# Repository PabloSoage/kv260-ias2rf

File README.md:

# KV260-IAS2RF — an RF front-end carrier for the AMD Kria KV260

**Status (12 November 2026): schematic and layout complete, on 8 layers. The board is fully routed, with zero
DRC errors and zero schematic-parity problems. It has not been fabricated, and no hardware has
been validated.** A few review items remain before an order (see [Status](#status)).

> **Rev06 (14 November 2026), now on `main`; Rev05 is tag `rev05`.** Rev06 gives Gigabit Ethernet its own FPGA pins, so the IAS1 link keeps
> both uplink lanes and its downlink and Ethernet adds about 1 Gb/s on top: either path works alone, both
> together carry about 3 Gb/s, with failover in the gateware ([CONTROL_SPEC §8](docs/CONTROL_SPEC.md),
> [fpga/eth/REV06.md](fpga/eth/REV06.md)). It also adds a 5 V fan header for enclosure v2
> ([ENCLOSURE §6](docs/ENCLOSURE.md)). Routed with zero DRC errors and zero parity problems. The full pre-order
> review (RF, power, ESD, thermal, routing, the enclosure's 3-D FEA with the boards, and the two-FPGA system
> simulation) is [docs/REV06_REVIEW.md](docs/REV06_REVIEW.md).

An adapter board for the **AMD Kria KV260 Vision AI Starter Kit**. It plugs into the KV260's IAS1
camera connector and carries the converters, a common clock and a front-end FPGA. It serves two
signal chains:

- **Software-defined radio**: HF, AM, FM, airband, amateur bands and PMR446. Receive, and
  transmit on the bands a licence covers.
- **Radar at 10.5 GHz**: the IF of the X-band chain from the open
  [AERIS-10 / PLFM_RADAR](https://github.com/NawfalMotii79/PLFM_RADAR) project, with ADAR1000
  beamforming. The 10.5 GHz chain itself is reused from AERIS-10, not redesigned here. The board
  is sized for 8 ADAR1000s (32 channels), so it covers both the Nexus variant (4 chips) and the
  Extended one (8 chips).

> ### The finding that shapes the whole project
>
> The **IAS0 (J7) connector on the KV260 does not reach the programmable logic**: its MIPI lanes
> run into an AP1302 ISP soldered on the carrier card. Only **IAS1 (J8)** is wired straight to
> the SOM. On top of that, **the KV260 has no 40-pin Raspberry Pi header** (J9 is a 15-pin
> camera connector), and **the GTH transceivers are not exposed**.
>
> The real I/O budget between a KV260 and an external board is **8 differential pairs and about
> 14 single-ended signals**. That is why the board has its own FPGA. The evidence and sources are
> in [docs/BLOCKERS_AND_RISKS.md](docs/BLOCKERS_AND_RISKS.md).

---

## The board at a glance

| | |
|---|---|
| Size | 119 × 132 mm, 140 × 132 with the RJ45's tab. It mounts on the KV260's IAS connectors and corner holes and overhangs to one side ([INTERFACE_SPEC §5.3](docs/INTERFACE_SPEC.md)) |
| Stackup | 8 layers, JLCPCB JLC08161H-2116C: signal, GND, signal, split power, GND, signal, GND, signal ([LAYOUT §3](docs/LAYOUT.md); 6 layers until 12 Nov, [compared in EIGHT_LAYERS](docs/EIGHT_LAYERS.md)) |
| Parts | 534 fitted: the top face, plus 20 on the bottom face under the FPGA (LVDS terminations and VCCINT caps); 4 DNP for the Ethernet option |
| Front-end FPGA | Xilinx XC7A50T-2FTG256I (the same part as AERIS-10) with a 128 Mb QSPI flash, plus JTAG |
| Radar ADC | AD9484, 8 bit, 400 MSPS, driven by two cascaded AD8352s |
| SDR ADC | AD9253, 14 bit, two channels at 62.5 MSPS (one LVDS lane each) |
| Radar DAC | AD9708, with reconstruction filter and balun |
| SDR DAC | AD9767, dual 14 bit, two output chains |
| Clock | Si549 programmable XO (400 or 500 MHz, GPS-disciplinable) into an ADCLK948 LVPECL fan-out |
| RF routing | Four M3SWA2-34DR+ SPDT switches and ten edge SMAs, plus two clock SMAs |
| Link to the Kria | IAS1 (Hirose BM20B), five LVDS pairs at up to 1 Gb/s each, AC-coupled; the Pmod J2 for control |
| Ethernet (option) | Gigabit RJ45 through an RTL8211FSI SGMII PHY, which shares two of the link's pairs: fit C1218–C1221 and remove C101, C102, C107, C108 to use it ([CONTROL_SPEC §7](docs/CONTROL_SPEC.md)) |
| To AERIS-10 | 2×20 IDC ribbon for eight ADAR1000s |
| Power | 12 V in; buck and LDO tree for 5 V, 3.3 V, 2.5 V, 1.8 V and 1.0 V, plus −3.3 V for the switches |

```mermaid
flowchart LR
  KV260["Kria KV260<br/>(K26 SOM)"] <-- "IAS1: 5 LVDS pairs<br/>Pmod: control" --> FPGA["XC7A50T<br/>front-end FPGA"]
  FPGA <-- LVDS --> ADCR["AD9484<br/>radar ADC"]
  FPGA <-- LVDS --> ADCS["AD9253<br/>SDR ADC"]
  FPGA --> DACR["AD9708<br/>radar DAC"]
  FPGA --> DACS["AD9767<br/>SDR DAC"]
  CLK["Si549 + ADCLK948<br/>clock"] --> ADCR & ADCS & DACR & DACS & FPGA
  ADCR & ADCS & DACR & DACS <--> RF["RF switches<br/>10 SMAs"]
  FPGA <-- "IDC ribbon" --> AERIS["AERIS-10<br/>8 × ADAR1000"]
  RF <--> AERIS
```

| Top | Bottom |
|---|---|
|  |  |

The renders come from KiCad. Some parts have no 3D model, so they show only their pads (the FPGA's
BGA, for one).

---

## Schematics and layout

- **[Schematic, all 10 sheets (PDF)](docs/CSI2-KRIA-KV260_Rev04_schematic.pdf)**
- **[Layout, the eight copper layers and both silkscreens (PDF)](docs/CSI2-KRIA-KV260_Rev04_layout.pdf)**
- KiCad 10 sources: [`CSI2-KRIA-KV260_Rev01.kicad_pro`](CSI2-KRIA-KV260_Rev01.kicad_pro), the root
  schematic and [`rev03/`](rev03/) (the nine sheets), the board
  [`CSI2-KRIA-KV260_Rev01.kicad_pcb`](CSI2-KRIA-KV260_Rev01.kicad_pcb), and the project's own
  symbols and footprints in [`symbols/`](symbols/) and [`footprints/`](footprints/). The file names
  keep the Rev01 name of the board they started from, and the sheets sit in `rev03/` where they
  were drawn; the contents are Rev04 (the 8-layer board, 12 Nov 2026).

| Sheet | Contents | Specification |
|---|---|---|
| [Root](docs/img/sch/ROOT.png) | Sheet hierarchy and the interface nets | [ARCHITECTURE](ARCHITECTURE.md) |
| [IAS_LINK](docs/img/sch/IAS_LINK.png) | The Hirose connectors, AC coupling and terminations of the link | [IAS_LINK_SPEC](docs/IAS_LINK_SPEC.md) |
| [CLOCK](docs/img/sch/CLOCK.png) | Si549, reference select and LVPECL fan-out | [CLOCK_SPEC](docs/CLOCK_SPEC.md) |
| [ADC_RADAR](docs/img/sch/ADC_RADAR.png) | AD9484 and its two AD8352 drivers | [ADC_RADAR_SPEC](docs/ADC_RADAR_SPEC.md) |
| [ADC_SDR](docs/img/sch/ADC_SDR.png) | AD9253, two channels | [ADC_SDR_SPEC](docs/ADC_SDR_SPEC.md) |
| [DAC_RADAR](docs/img/sch/DAC_RADAR.png) | AD9708, filter and balun | [DAC_RADAR_SPEC](docs/DAC_RADAR_SPEC.md) |
| [DAC_SDR](docs/img/sch/DAC_SDR.png) | AD9767 in interleaved mode, two output chains | [DAC_SDR_SPEC](docs/DAC_SDR_SPEC.md) |
| [ROUTING](docs/img/sch/ROUTING.png) | Four RF switches and the SMAs | [ROUTING_SPEC](docs/ROUTING_SPEC.md) |
| [CONTROL](docs/img/sch/CONTROL.png) | The front-end FPGA: banks, configuration, Pmod, AERIS ribbon, housekeeping | [CONTROL_SPEC](docs/CONTROL_SPEC.md) |
| [POWER](docs/img/sch/POWER.png) | The power tree | [POWER_SPEC](docs/POWER_SPEC.md) |

---

## Status

| Check | Result |
|---|---|
| ERC | 0 errors; 7 warnings, all explained: configuration and XADC pins tied to power on purpose ([CONTROL_SPEC §5](docs/CONTROL_SPEC.md)) |
| DRC, zones refilled | **0 violations, 0 unrouted connections, 0 schematic-parity problems** (12 Nov, on 8 layers) |
| Signal and power integrity | Reviewed on 11 Nov and re-run on 8 layers on 12 Nov, ideal / 6 / 8 layers side by side ([EIGHT_LAYERS.md](docs/EIGHT_LAYERS.md), [SIGNAL_INTEGRITY.md](docs/SIGNAL_INTEGRITY.md)): SMA launch in openEMS (S11 −30.9 dB at 1 GHz with the ESD diode), LVDS eyes within 1–26 mV of ideal except LINK_RX_D0 (−52 mV), worst intra-pair skew 9 ps, VCCINT under its target to 100 MHz with four caps under the BGA; ESD protection on every SMA, the Pmod and JTAG, a GND via within 3 mm of every LVDS layer change, exposed-pad vias and an edge fence |
| Planes | L2 and L5 carry only ground, no supply track (`_work/layout/planechk.py`); every supply pin reaches its island (the DRC's zero unrouted) |
| Mechanical fit | Registered on AMD's 3D model of the KV260: the mounting holes land within 5 µm ([INTERFACE_SPEC §5.3](docs/INTERFACE_SPEC.md)) |

**Open before ordering** ([docs/LAYOUT.md §6.2–6.3](docs/LAYOUT.md)):

1. **The rest of the board, reviewed on 12 Nov** ([SIGNAL_INTEGRITY §9](docs/SIGNAL_INTEGRITY.md)).
   - **Fixed.** The router had necked supply tracks and the bucks' switch nodes to 0.1 mm: 1.6 A
     through 0.1 mm at U1001, and a 251 mV drop on the ADCs' +1V8_A. The supply tracks are now
     widened (865 mm at ≥ 0.5 mm, against 119), and +1V8_A starts at 1.85 V to cover what is
     left of the drop.
   - **Analogue nodes.** Digital tracks beside the analogue nodes are down to 81 mm within
     0.3 mm, from 91. Most of what was left was where the SDR DAC's filters crossed the DAC bus.
     On 12 Nov DAC2's filter was re-placed next to its balun and DAC1's middle node re-routed as
     a pair: their digital neighbours went from 59 mm to 14 mm. DAC2's common mode at the balun
     fell by 9–21 dB. On 13 Nov DAC1's filter followed, onto the bottom face under T801 (its
     middle node 51 → 3 mm, common mode 1–6 dB lower), the reference oscillator's pair was
     coupled and matched, and the SDR ADC's input network was simulated: its copper costs
     nothing in band, so it stays.
   - **Thermal.** 7.5 W on 134 cm² in still air (with the Ethernet PHY): +27 °C mean and +51 °C at the clock buffer. Fine
     on the bench. A vehicle install needs airflow or a path to the enclosure.
2. **Ten of the 19 LVDS pairs are not coupled** (11 of 22 counting U401's three clock pairs:
   `CLK_ADCS` and `CLK_FPGA` were re-routed as coupled pairs on 12 Nov, `CLK_FPGA` after its
   four pad resistors were re-placed together; SIGNAL_INTEGRITY §9.4). Since 12 Nov the board has 8 layers and nine pairs
   run coupled at 100 Ω end to end ([EIGHT_LAYERS.md](docs/EIGHT_LAYERS.md)). The other ten are
   two 50 Ω legs matched to ±5 ps, within 1–26 mV of their ideal eye except LINK_RX_D0 (−52 mV).
   LINK_RX leaves bank 34, the only 2.5 V bank, in the BGA's south-east corner, and crosses every
   ADC pair to AC capacitors spread 9 mm apart; moving it to the bank's outer balls was tried on
   12 Nov and dropped (the corner has no room left for the vias). Coupling it would need the
   capacitors at J101 moved together first.
3. **ADCR data to DCO skew, −90 to +5 ps** (was −177 to −28). DCO's legs are swapped at the FPGA
   (N14 = DCO_N, P14 = DCO_P) so the pair reaches the AD9484 the right way round without going
   round the chip: 39 mm instead of 51. **The gateware must invert that clock** (ISERDESE2
   `IS_CLK_INVERTED`, or capture on the other edge) ([CONTROL_SPEC §1](docs/CONTROL_SPEC.md)).
   The rest is inside IDELAYE2's range and calibrated per bit.
4. **Order the 2116C stack explicitly** (JLC08161H-2116C): the widths are solved for it
   ([FABRICATION.md](docs/FABRICATION.md)). Five 8-layer bare boards: $287.96 at 140 × 132 mm with the Ethernet tab ($282.92 without it, $236.88 on 6 layers).
5. **The Kria side of the link is `DIFF_SSTL12`, not `LVDS_12`** (UG571 read on 12 Nov,
   [INTERFACE_SPEC §6.3](docs/INTERFACE_SPEC.md)). No `LVDS_12` exists. `LVDS` at 1.2 V is
   input-only with no internal termination. `DIFF_SSTL12` has on-die split termination
   (`RTT_48`, about 96 Ω biased at 0.6 V) and drives through `RDRV_60_60`. No change to the board.
   Still to confirm in DS925: its input threshold and the −2LV rate ceiling. The link carries 2 Gb/s towards the Kria and 1 Gb/s back (two of its five
   pairs are clocks), with a ceiling of about 1.25 Gb/s per pair set by the silicon
   ([IAS_LINK_SPEC §7](docs/IAS_LINK_SPEC.md)).
6. **3-D full-wave sub-models (openEMS), not yet inside the eye simulation.**
   - **Layer change L1 to L6.** The pair reflects under −29 dB up to 1.25 GHz, with or without
     ground vias. Without them 7 % of the common mode's power leaks into the plane cavity; with
     two, 1 %.
   - **BGA escape.** The 0.10 mm necks reflect under −24 dB at 1.25 GHz.
   - **Two pairs side by side.** The board's worst run couples 1.9 % of a 300 ps edge onto the
     nearest leg, not the 7 % the 2-D estimate gave.
   - **J101's footprint**, from the Hirose pins to the AC capacitors: reflection under −25 dB to 1.25 GHz,
     but the legs' different escapes turn 9 % of the differential wave into common mode.

   Done, in [SIGNAL_INTEGRITY §9.6](docs/SIGNAL_INTEGRITY.md):
   - **Receive budgets.** Radar: full scale −17.6 dBm, NF 26.8 dB. SDR: full scale −2.4 and
     −3.0 dBm, NF 22 dB. On both, the ADC is 80–92 % of the noise.
   - **Transmit levels** and **the DAC filters with their copper.**
   - **The board's thermal map**, with junctions for every part that has data. At 25 °C in still
     air, the hottest junction is the ADCLK948 at 84 °C and the FPGA is at 63 °C. A vehicle
     needs airflow: a heatsink on the ICs and the regulators, with a fan, keeps every junction
     under 92 °C at 70 °C ambient.

   The first boards are for evaluation.
7. **The AERIS-10 end of the ribbon does not exist yet.**
8. **No firmware.** The FPGA design for the front end and the Kria side of the link are not
   written yet.

**Cost** ([docs/JLCPCB_QUOTE.md](docs/JLCPCB_QUOTE.md), bare boards re-quoted on 8 layers on 12 Nov 2026): about **$2,070 for two
assembled boards** and $4,240 for five, three quarters of it parts. Seven parts are out of stock at
LCSC today (the ADCs, the RF switches, the clock buffer, the DAC, a balun and the drivers): JLCPCB's
global sourcing or consigned parts cover them.

---

## Documentation

| Document | Contents |
|---|---|
| **[docs/VEHICLE_PLATFORM.md](docs/VEHICLE_PLATFORM.md)** | **System view.** The whole vehicle project: LiDAR, SDR, radar, OBD2 |
| [docs/SHOPPING_LIST.md](docs/SHOPPING_LIST.md) | Parts and checklist per stage, with indicative costs |
| [ARCHITECTURE.md](ARCHITECTURE.md) | Master document for this board: the Rev03 architecture and BOM |
| [docs/BLOCKERS_AND_RISKS.md](docs/BLOCKERS_AND_RISKS.md) | The five blockers, closed, with evidence and sources, plus the open risks |
| [docs/INTERFACE_SPEC.md](docs/INTERFACE_SPEC.md) | Pin map for J8 and the Pmod, the mechanical envelope, the adapter registered on the KV260 model |
| [docs/POWER_AND_STACKUP.md](docs/POWER_AND_STACKUP.md) | Per-rail current budget and the original 6-layer stackup with computed trace widths |
| [docs/SYMBOLS.md](docs/SYMBOLS.md) | The project's symbols, each from its datasheet, cross-checked against a second source where one exists |
| Sheet specifications | One per schematic sheet, in the table above: every value and where it comes from |
| [docs/LAYOUT.md](docs/LAYOUT.md) | The board: outline, stackup, rules, the split power layer, placement, routing and the LVDS review |
| [docs/EIGHT_LAYERS.md](docs/EIGHT_LAYERS.md) | The 8-layer board against the 6-layer one: stacks, every check side by side, eyes, skew, PDN, SMA, and what the same corrections would give on 6 layers |
| [docs/SIGNAL_INTEGRITY.md](docs/SIGNAL_INTEGRITY.md) | The RF/high-speed review (11 Nov) and the 8-layer re-run (12 Nov, §8): impedance, SMA launch (openEMS), LVDS eyes (ngspice), PDN impedance and DC drop, crosstalk, return vias, what is still a compromise; figures and data in [docs/sim/](docs/sim/) |
| [docs/FABRICATION.md](docs/FABRICATION.md) | Ordering from JLCPCB: the output script, the order form, what is left for the day of the order |
| [docs/JLCPCB_QUOTE.md](docs/JLCPCB_QUOTE.md) | What the JLCPCB order would cost (10 Nov 2026, bare boards on 8 layers 12 Nov, re-quoted with the Ethernet tab 13 Nov): boards, assembly fees and every part with its LCSC link and price. About $2,125 for two assembled boards, $4,310 for five |
| [docs/ROADMAP.md](docs/ROADMAP.md) | Staged plan with verifiable exit criteria |
| [docs/AUDIT_Rev01.md](docs/AUDIT_Rev01.md), [docs/HISTORY_Rev01.md](docs/HISTORY_Rev01.md) | What the inherited files contained, and the record of the earlier work |

---

## Repository layout

| Path | Contents |
|---|---|
| `CSI2-KRIA-KV260_Rev01.*`, `rev03/` | The KiCad project: root schematic, nine sheets, board |
| `symbols/`, `footprints/` | The project's own libraries |
| `docs/` | Specifications, layout and fabrication notes, renders and the PDFs |
| `_work/` | The scripts behind every finding and every step of the layout: symbols and footprints, sheet checks, placement (`_work/layout/build_board.py`), plane and LVDS checks, fabrication outputs |
| `fab/` | Not tracked. `python _work/fab/make_fab.py` writes Gerbers, drill, BOM and CPL there for JLCPCB |
| `PCB/`, `Documents/` | The original Allied Vision sources (Altium) and their outputs, untouched |
| `_backup_original/`, `_deprecated/` | Snapshots of the inherited files and the sheets removed from the project |

Reproducing the checks and the outputs (KiCad 10):

```bash
kicad-cli sch erc --severity-all CSI2-KRIA-KV260_Rev01.kicad_sch
kicad-cli pcb drc --schematic-parity --refill-zones --severity-all CSI2-KRIA-KV260_Rev01.kicad_pcb
python _work/fab/make_fab.py                                   # fab/: Gerbers, drill, BOM, CPL
python _work/fab/quote.py                                      # today's LCSC prices and stock; refreshes docs/JLCPCB_QUOTE.md
python _work/layout/lvds_skew.py CSI2-KRIA-KV260_Rev01.kicad_pcb  # LVDS delays, skew and stubs; --stubs PS lists the branches (needs shapely)
```

---

## Related work

The DSP core this board will need already exists, runs on real silicon and is published
separately:

**[scanner64](https://github.com/PabloSoage/scanner64)**: a real-time multichannel DDC bank for
the KV260's PL. Measured on the board: 100.05 MSPS sustained, no samples dropped across
200 million, bit-exact against its Python model, 8.38 mW per channel, 169.9 MHz Fmax post-route.

That project answers, with hardware, the question this board is built around: whether the PL can
sustain a converter stream in real time. It can.

---

## Where the project came from, and attribution

This is a **fork** of the open hardware design
[Allied Vision Adapter Board CSI-2 for Kria KV260](https://github.com/alliedvision), published
under the MIT licence (see [LICENSE](LICENSE)). What is kept from that design:

- the board's mechanical fit to the KV260 (the outline was extended)
- the two Hirose BM20B(0.8)-34DP connectors (IAS0 / IAS1) and their wiring to the SOM

Everything else (the MIPI camera electronics, level shifters, USB power) was removed and replaced
by the RF chain described here. **This repository no longer produces an Allied Vision camera
adapter board.** If that is what you want, use the original project.

---

## Simulation results

Every figure compares three cases: an **ideal** line, the board on **6 layers** (JLC06161H-2116A,
11 November 2026) and on **8 layers** (JLC08161H-2116C, the board in this repository), all run
through the same scripts. The full comparison is in [docs/EIGHT_LAYERS.md](docs/EIGHT_LAYERS.md),
the method in [docs/SIGNAL_INTEGRITY.md](docs/SIGNAL_INTEGRITY.md).

| Check | 6 layers | 8 layers |
|---|---|---|
| Pairs routed coupled | 0 of 19 | 9 of 19 |
| Worst intra-pair \|P−N\| | 84 ps | 9 ps |
| Eye lost to routing (routed − ideal) | mean −22 mV, worst −113 mV | mean −8 mV, worst −52 mV |
| Zero-crossing spread added | mean 5 ps, worst 29 ps | mean 1 ps, worst 10 ps |
| Layer changes with no GND via within 3 mm | 1 of 186 | 0 of 89 |
| Other pairs' legs within 0.25 mm | 97.6 mm | 65.8 mm |
| Signal tracks on L4 under the BGA | 64 segments | 3 (supply stubs) |
| ADCR data − DCO | −88 … −23 ps | −90 … +5 ps (DCO re-routed 12 Nov; IDELAY absorbs it) |
| VCCINT impedance, max in band / at 100 MHz (target 120 mΩ) | 51 / 61 mΩ | 41 / 63 mΩ |
| DC drop +2V5 at 601 mA | 173–185 mV | 122–129 mV |
| SMA launch S11 at 1 / 3 GHz, with the ESD diode | −30.6 / −13.5 dB | −30.9 / −13.7 dB |

**LVDS eyes** (ngspice, PRBS7 at 1 Gb/s, each leg's copper by layer and width). The ideal line
depends on each board's pair length and termination, so each board is shown against its own ideal.

| Pair | 6 layers: ideal / routed | 8 layers: ideal / routed |
|---|---|---|
| LINK_RX_D1 | 575 / 559 mV, 75 / 77 ps | 385 / 372 mV, 41 / 51 ps |
| LINK_RX_D0 | 607 / 559 mV, 35 / 30 ps | 509 / 457 mV, 25 / 31 ps |
| LINK_RX_CLK | 548 / 516 mV, 12 / 14 ps | 395 / 392 mV, 10 / 10 ps |
| ADCS_FCO | 648 / 650 mV, 49 / 46 ps | 628 / 617 mV, 17 / 17 ps |
| ADCR_DCO | 626 / 581 mV, 24 / 35 ps | 609 / 610 mV, 17 / 18 ps |

Eye opening at the centre of the bit, then zero-crossing spread. The LINK_RX eyes end at the AC
capacitors, not at the Kria's receiver, so they are indicative only; the opening is in every case
several times the receiver's ±100 mV threshold.

**Eye opening and zero-crossing spread** of every pair, three cases.

**Intra-pair skew**, ball to pad, with the FPGA's package delay.

**Power distribution** seen from the XC7A50T's balls. The L4/L5 plane pair keeps its spacing, so
the impedance barely moves.

**Edge SMA launch** (openEMS FDTD) with its ESD diode. The outer prepreg is the same on both
stacks, and so is the launch.

**DAC reconstruction filters** (ngspice), ideal and with each node's copper. The cut-off moves 4–9 %
down and the passband does not change. Below, the common mode at the balun before and after the
re-placement of 12 Nov ([SIGNAL_INTEGRITY §9.3](docs/SIGNAL_INTEGRITY.md)).

**Board temperature** at 25 °C ambient in still air: a 2-D model with each layer's real copper,
convection from both faces, and the power budget's 7.5 W (re-run 13 Nov with the Ethernet PHY)
([SIGNAL_INTEGRITY §9.6](docs/SIGNAL_INTEGRITY.md)).

**Five ways of cooling it**, on one colour scale: still air, a fan, a passive heatsink on the four
main ICs, the same with the regulators, and heatsink plus fan
([SIGNAL_INTEGRITY §9.6](docs/SIGNAL_INTEGRITY.md)).

**An LVDS pair changing layer**, L1 to L6 through two vias, in 3-D (openEMS), four via
arrangements ([SIGNAL_INTEGRITY §9.6](docs/SIGNAL_INTEGRITY.md)).

**The other 3-D sub-models**: the BGA escape, J101's pins to the AC capacitors, two pairs side by
side, and the common mode through the layer change
([SIGNAL_INTEGRITY §9.6](docs/SIGNAL_INTEGRITY.md)).

**The Ethernet option** shares two link pairs through unfitted capacitors: what their branches cost
the IAS1 link, where C1218 went, and the Ethernet paths themselves
([SIGNAL_INTEGRITY §9.7](docs/SIGNAL_INTEGRITY.md)).

---

## Mounted on the KV260

A printed base holds the KV260 and the adapter together: posts in place of the carrier's rubber feet,
posts under the overhang, a wall that takes the SMA cables' torque, and a pedestal and strap that
carry the Ethernet tab ([MECHANICAL](docs/MECHANICAL.md); STLs in `mech/`). Rendered in Blender
(Cycles) with AMD's KV260 model.

| The RJ45 tab, pedestal and strap | The SMA wall |
|---|---|
|  |  |

---

## The enclosure

A closed printed case for vehicle use ([ENCLOSURE](docs/ENCLOSURE.md); STLs in `mech/`). It has a tray and a
lid that close on six lugs, with printed snap pins for a tool-free fit test or stainless M4 screws. The SMA
bodies are clamped in the split line. A honeycomb floor and TPU-padded clamp posts hold both boards without
play. Optional TPU 95A corner bumpers are for handling. It prints on a Bambu A1 in PETG-CF, ASA or PAHT-CF.

| Opened | Section through the boards |
|---|---|
|  |  |
| **The tray: honeycomb, posts, pockets** | **The lid from inside: clamp posts and pads** |
|  |  |
| **The KV260 side: one cut-out per connector** | **The SMA side** |
|  |  |

### Version 2: with a fan, for hot vehicles

Version 2 adds a 50 × 50 × 10 mm 5 V fan in the lid. It blows through a removable
100-mesh filter onto the adapter's hot strip, where the clock, the converters and the Ethernet PHY sit. The board's
fan header J1002 powers it. The SMA-side vents are closed, so the fan pressurises the case and the air leaves through
17 slots in the right wall. With the three small heatsinks on the clock chips and the ADC, every adapter IC stays
within its limit even at 70 °C ambient, according to a 3-D CFD of the case as built
([ENCLOSURE §6](docs/ENCLOSURE.md), [thermal study](docs/ENCLOSURE_V2_THERMAL.md#verification-of-the-built-v2)).

| Closed: the filtered fan grille on the lid | The lid from inside: fan, duct and screw bosses |
|---|---|
|  |  |

### Strength: 3-D finite elements, case and boards together

The printed case with both boards inside, meshed in 3-D (197 k tetrahedra) and loaded with 50 g, held at its four
ears ([ENCLOSURE §5.3](docs/ENCLOSURE.md)). The case stays below 3.6 MPa nearly everywhere. Its peak is 9.2 MPa, on
the rib above the right rear ear, still a factor 1.9 under the material's strength at 70 °C. The boards bow by
0.16 mm and see at most 162 µε at the BGAs, against a 500 µε guide for solder joints under shock.

Earlier beam-and-plate FEA of the case with the boards in it, per material, at 23 °C and 70 °C:
- first mode;
- a 50 g shock;
- a 1 m corner drop, bare and with the bumpers;
- off-road vibration fatigue.

Method, assumptions and the full table are in [ENCLOSURE §5](docs/ENCLOSURE.md#5-simulation-calculix). The
case passes shock and vibration in PETG-CF, ASA and PAHT-CF. A bare 1 m drop needs the bumpers.

---

## Legal notice

This design transmits on regulated bands. Operating the SDR transmitter requires an amateur radio
licence or equivalent authorisation, and emission in 10.4–10.6 GHz is subject to national
allocations that are **not** free to use in every country. See the compliance section of
[ARCHITECTURE.md](ARCHITECTURE.md). Staying within the applicable law is the responsibility of
whoever builds and operates the equipment.

## Licence

MIT — see [LICENSE](LICENSE). The licence and attribution of the original Allied Vision project
are preserved.

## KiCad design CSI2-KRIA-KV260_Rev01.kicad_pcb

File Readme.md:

# KV260-IAS2RF — Front-End RF unificado (SDR + Radar FMCW banda X) para AMD Kria KV260

**Estado: diseño en curso (Rev02, fase de arquitectura). No fabricable. No hay hardware validado.**

Este repositorio contiene el desarrollo de una placa adaptadora para la **AMD Kria KV260 Vision
AI Starter Kit** que se acopla por los conectores Hirose de las interfaces IAS y aloja los
conversores, el reloj común y una **FPGA de front-end**, dando servicio a dos cadenas:

- **Canal 1 — SDR multibanda:** walkie, HF, AM, FM, VHF/UHF. Recepción y transmisión
- **Canal 2 — radar 10.5 GHz:** IF de la cadena de banda X del proyecto abierto
  [AERIS-10 / PLFM_RADAR](https://github.com/NawfalMotii79/PLFM_RADAR), con beamforming sobre
  ADAR1000

La cadena de 10.5 GHz **no se rediseña aquí**: se reutiliza AERIS-10. La placa se dimensiona para
**8 ADAR1000 (32 canales)**, de modo que soporte tanto la variante Nexus (4 chips) como la
Extended (8 chips).

> ### Hallazgo que condiciona todo el proyecto
>
> El conector **IAS0 (J7) de la KV260 no llega a la lógica programable**: sus carriles MIPI
> entran en un ISP AP1302 soldado en la carrier card. Solo **IAS1 (J8)** está cableado
> directamente al SoM. Además, **la KV260 no tiene ninguna cabecera Raspberry Pi de 40 pines**
> (J9 es un conector de cámara de 15 pines) y **los transceptores GTH no son accesibles**.
>
> El presupuesto real de E/S entre la KV260 y una placa externa es de **8 pares diferenciales y
> ~14 señales sueltas**. De ahí la FPGA de front-end. Ver [docs/RIESGOS.md](docs/RIESGOS.md).

## Origen del proyecto y atribución

Este proyecto es un **fork** del diseño de hardware abierto
[Allied Vision Adapter Board CSI-2 for Kria KV260](https://github.com/alliedvision), publicado
bajo licencia MIT (ver [LICENSE](LICENSE)). De aquel diseño se conserva:

- La geometría de la placa y su acoplamiento mecánico a la KV260
- Los dos conectores Hirose BM20B(0.8)-34DP (IAS0 / IAS1) y su cableado a la SoM
- El stackup y las reglas de fabricación originales

Todo lo demás (electrónica de cámara MIPI, level shifters, alimentación USB) se ha eliminado y
se sustituye por la cadena de RF descrita en la documentación. **Este repositorio ya no produce
una placa adaptadora de cámaras Allied Vision.** Si buscas eso, usa el proyecto original.

## Documentación

| Documento | Contenido |
|---|---|
| **[HANDOFF.md](HANDOFF.md)** | **Empieza aquí si retomas el proyecto.** Resumen autocontenido: estado, hallazgos, decisiones pendientes y reglas de trabajo |
| **[docs/PLATAFORMA_4X4.md](docs/PLATAFORMA_4X4.md)** | **Visión de sistema.** Esta placa es un subsistema de una plataforma de sensores y comunicaciones para un 4×4 de expedición: LiDAR, SDR, radar, OBD2 |
| **[docs/LISTA_COMPRA.md](docs/LISTA_COMPRA.md)** | Lista de material y checklist por etapas, con costes orientativos |
| **[ARCHITECTURE_draft_es.md](ARCHITECTURE_draft_es.md)** | **Documento maestro.** Arquitectura Rev03: FPGA de front-end, enlace con la Kria, conversores, plan de frecuencias, integración con AERIS-10, BOM |
| [docs/AUDITORIA_Rev01.md](docs/AUDITORIA_Rev01.md) | Auditoría de los ficheros actuales: qué hay realmente en el repo frente a lo que la documentación anterior afirmaba |
| [docs/RIESGOS.md](docs/RIESGOS.md) | Bloqueantes y riesgos abiertos, priorizados, con acción concreta para cerrar cada uno |
| [docs/ROADMAP.md](docs/ROADMAP.md) | Plan de trabajo por fases con criterios de salida verificables |
| [docs/HISTORIAL_Rev01.md](docs/HISTORIAL_Rev01.md) | Registro del trabajo hecho sobre el Rev01 (purga del esquema original y generación por script), con su valoración |

**Empieza por [docs/RIESGOS.md](docs/RIESGOS.md)** si vas a retomar el proyecto: hay tres
incógnitas bloqueantes que condicionan la arquitectura y deben resolverse antes de tocar
un esquemático.

## Estado real de los ficheros de diseño

Los ficheros KiCad del repositorio corresponden al **Rev01-WIP**, un estado intermedio que
**no refleja la arquitectura Rev02** documentada aquí y que contiene errores de selección de
componentes ya identificados. En concreto:

| Fichero | Estado real |
|---|---|
| `CSI2-KRIA-KV260_Rev01-2.kicad_sch` | Esquema original purgado de electrónica de cámara. **Utilizable como base.** |
| `FRONTEND.kicad_sch` | Generado por script, sin revisión eléctrica. Contiene componentes descartados. **A rehacer.** |
| `PHASED_ARRAY.kicad_sch` | Generado por script. Los ADAR1000 no tienen alimentación conectada. **A rehacer.** |
| `CSI2-KRIA-KV260_Rev01.kicad_pcb` | Layout original + 34 footprints vacíos (sin pads ni nets) situados fuera del contorno de placa. **El placement no existe.** |
| `PCB/`, `Documents/` | Fuentes Altium y salidas de fabricación del diseño Allied Vision original, intactas. |

Detalle y evidencia en [docs/AUDITORIA_Rev01.md](docs/AUDITORIA_Rev01.md).

## Entorno

- **KiCad 10** para esquemático y layout (el proyecto se migró desde Altium Designer 22)
- Los ficheros Altium originales se conservan en `PCB/` como referencia histórica
- Los scripts de manipulación del Rev01 están en `_work/`; ver la nota metodológica en
  [docs/HISTORIAL_Rev01.md](docs/HISTORIAL_Rev01.md) antes de reutilizarlos

## Aviso legal

Este diseño transmite en bandas cuyo uso está regulado. La operación del transmisor SDR
requiere licencia de radioaficionado o autorización equivalente, y la emisión en 10.4–10.6 GHz
está sujeta a asignaciones nacionales que **no** son de uso libre en todos los países. Ver la
sección de cumplimiento normativo del documento maestro. La responsabilidad de operar dentro
de la legalidad aplicable es de quien construya y use el equipo.

## Licencia

MIT — ver [LICENSE](LICENSE). Se mantiene la licencia y la atribución del proyecto original de
Allied Vision.

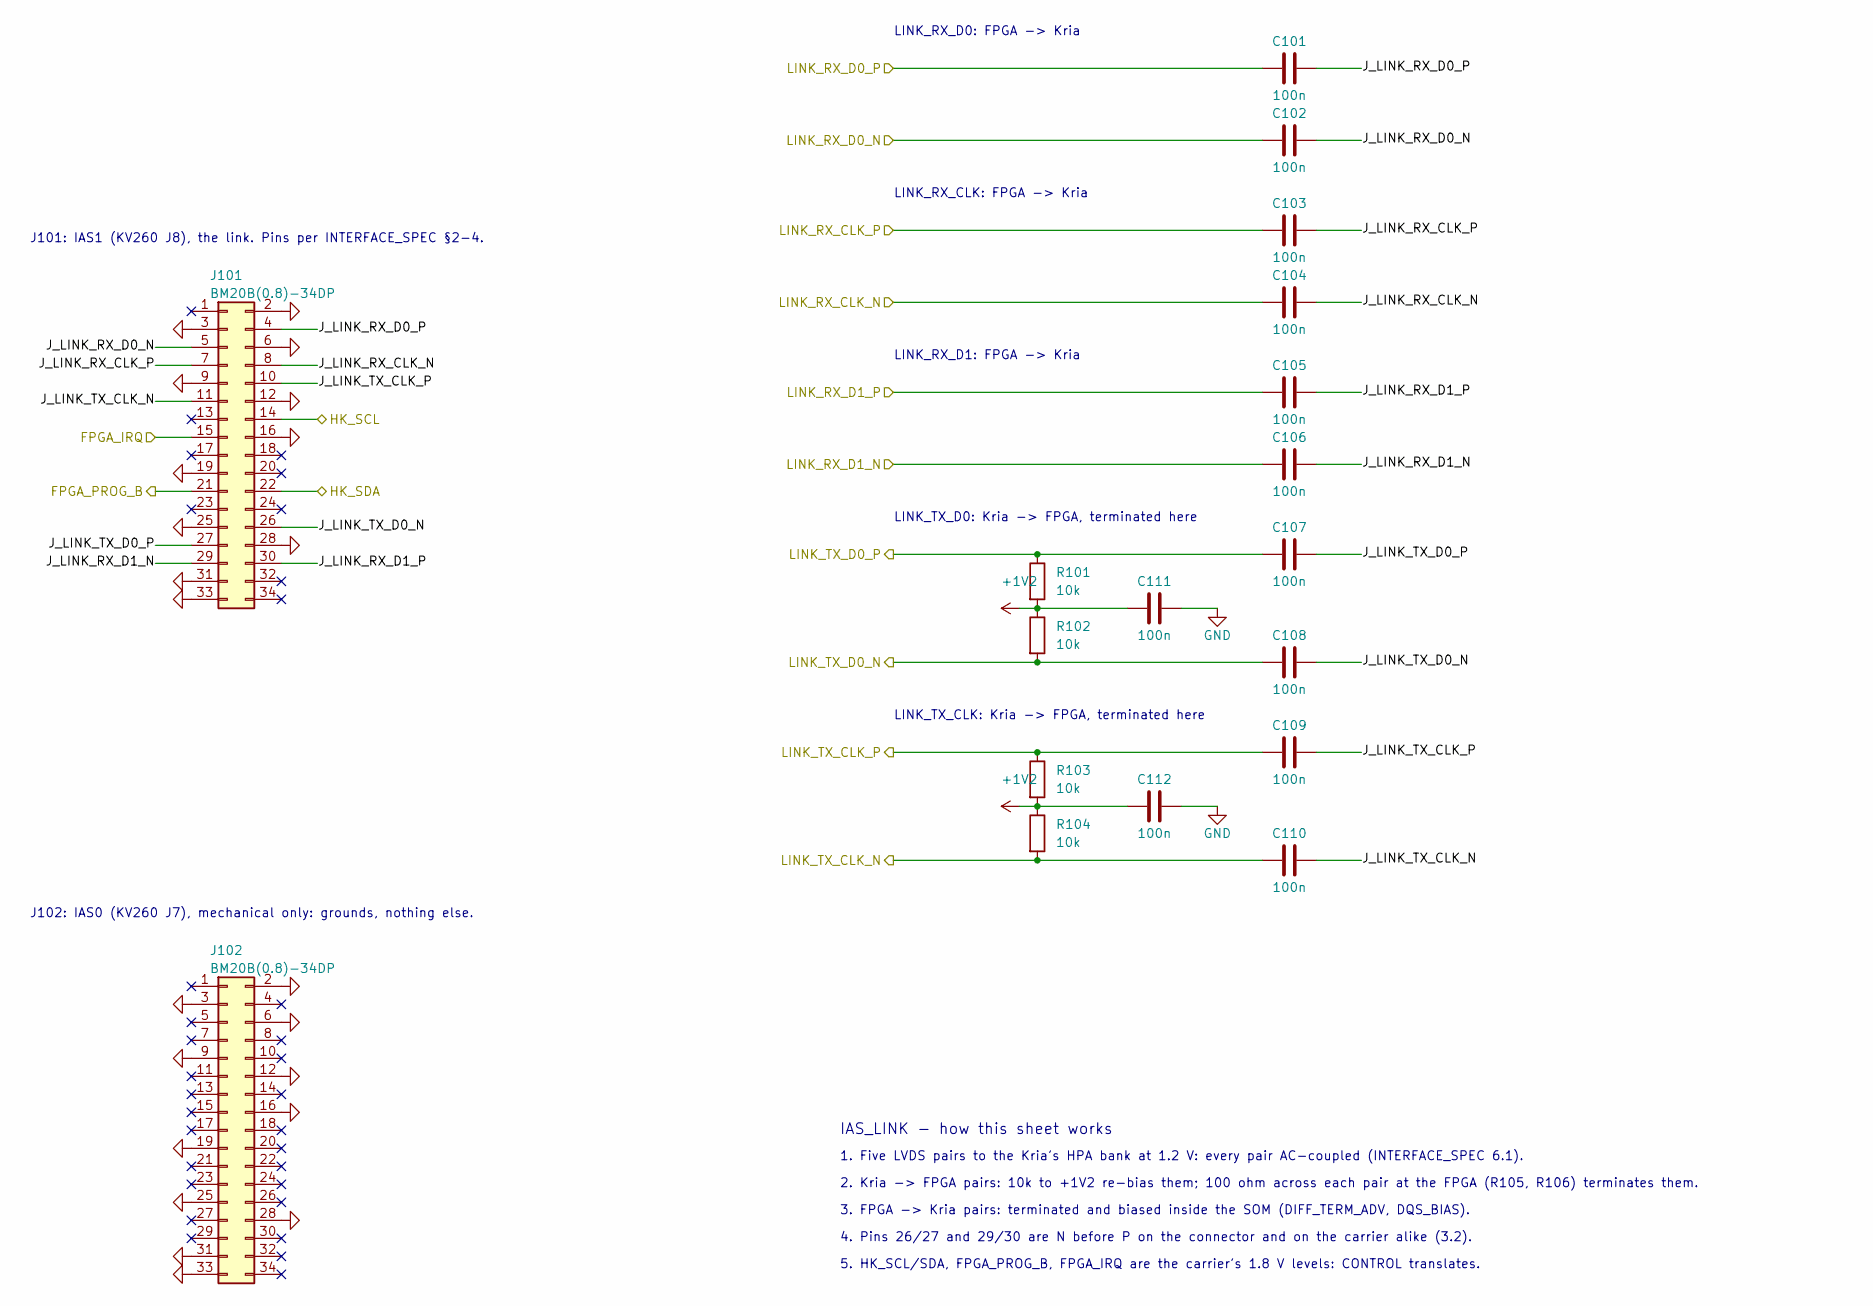
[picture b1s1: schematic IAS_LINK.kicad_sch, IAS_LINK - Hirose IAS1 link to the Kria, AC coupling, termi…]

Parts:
C101, C102, C103, C104, C105, C106, C107, C108, C109, C110, C111, C112: 100n; C_0402_1005Metric
J101, J102: BM20B(0.8)-34DP; J-BM20B(0.8)-34DP
R101, R102, R103, R104: 10k; R_0402_1005Metric

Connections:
+1V2: C111.1, C112.1, R101.2, R102.1, R103.2, R104.1; also elsewhere on the board
/FPGA_IRQ: J101.15; also elsewhere on the board
/FPGA_PROG_B: J101.21; also elsewhere on the board
/HK_SCL: J101.14; also elsewhere on the board
/HK_SDA: J101.22; also elsewhere on the board
/IAS_LINK/J_LINK_RX_CLK_N: C104.2, J101.8
/IAS_LINK/J_LINK_RX_CLK_P: C103.2, J101.7
/IAS_LINK/J_LINK_RX_D0_N: C102.2, J101.5
/IAS_LINK/J_LINK_RX_D0_P: C101.2, J101.4
/IAS_LINK/J_LINK_RX_D1_N: C106.2, J101.29
/IAS_LINK/J_LINK_RX_D1_P: C105.2, J101.30
/IAS_LINK/J_LINK_TX_CLK_N: C110.2, J101.11
/IAS_LINK/J_LINK_TX_CLK_P: C109.2, J101.10
/IAS_LINK/J_LINK_TX_D0_N: C108.2, J101.26
/IAS_LINK/J_LINK_TX_D0_P: C107.2, J101.27
/LINK_RX_CLK_N: C104.1; also elsewhere on the board
/LINK_RX_CLK_P: C103.1; also elsewhere on the board
/LINK_RX_D0_N: C102.1; also elsewhere on the board
/LINK_RX_D0_P: C101.1; also elsewhere on the board
/LINK_RX_D1_N: C106.1; also elsewhere on the board
/LINK_RX_D1_P: C105.1; also elsewhere on the board
/LINK_TX_CLK_N: C110.1, R104.2; also elsewhere on the board
/LINK_TX_CLK_P: C109.1, R103.1; also elsewhere on the board
/LINK_TX_D0_N: C108.1, R102.2; also elsewhere on the board
/LINK_TX_D0_P: C107.1, R101.1; also elsewhere on the board
GND: C111.2, C112.2, J101.2, J101.3, J101.6, J101.9, J101.12, J101.16, J101.19, J101.25, J101.28, J101.31, J101.33, J102.2, J102.3, J102.6, J102.9, J102.12, J102.16, J102.19, J102.25, J102.28, J102.31, J102.33; also elsewhere on the board

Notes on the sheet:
J101: IAS1 (KV260 J8), the link. Pins per INTERFACE_SPEC §2-4.
J102: IAS0 (KV260 J7), mechanical only: grounds, nothing else.
LINK_RX_D0: FPGA -> Kria
LINK_RX_CLK: FPGA -> Kria
LINK_RX_D1: FPGA -> Kria
LINK_TX_D0: Kria -> FPGA, terminated here
LINK_TX_CLK: Kria -> FPGA, terminated here
IAS_LINK - how this sheet works
1. Five LVDS pairs to the Kria's HPA bank at 1.2 V: every pair AC-coupled (INTERFACE_SPEC 6.1).
2. Kria -> FPGA pairs: 10k to +1V2 re-bias them; 100 ohm across each pair at the FPGA (R105, R106) terminates them.
3. FPGA -> Kria pairs: terminated and biased inside the SOM (DIFF_TERM_ADV, DQS_BIAS).
4. Pins 26/27 and 29/30 are N before P on the connector and on the carrier alike (3.2).
5. HK_SCL/SDA, FPGA_PROG_B, FPGA_IRQ are the carrier's 1.8 V levels: CONTROL translates.
